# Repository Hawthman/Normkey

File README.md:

A custom 48 key split keyboard.

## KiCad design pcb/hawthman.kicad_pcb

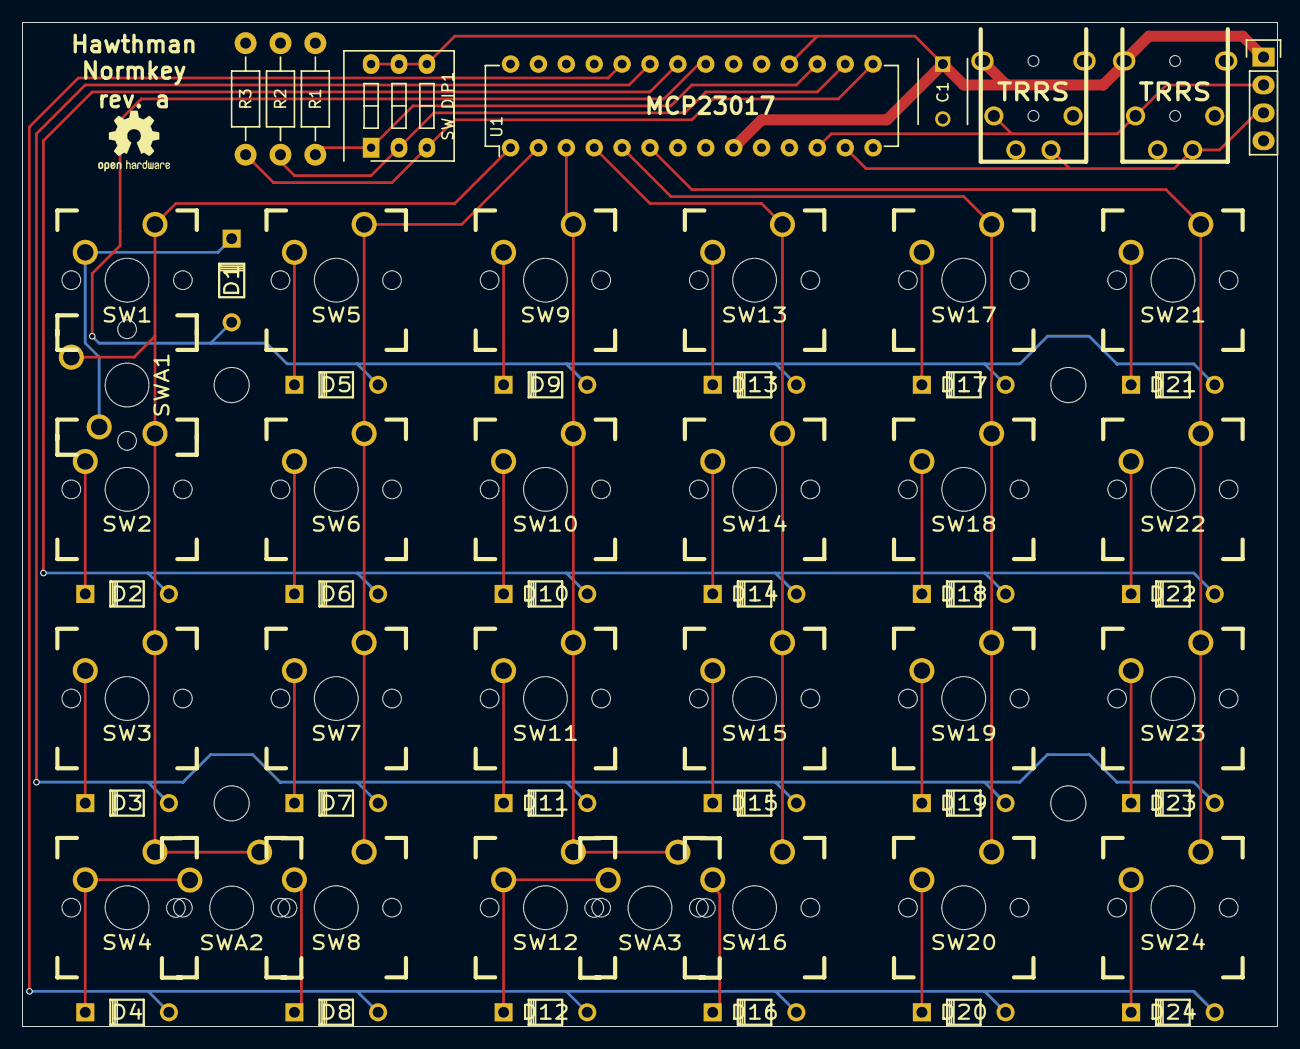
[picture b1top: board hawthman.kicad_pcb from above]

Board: 2 copper layers, 114.3 x 91.4 mm, 60 parts (0 on the bottom side), 41 nets.

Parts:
C1: 0.1uF; C_Disc_D6_P5
D1, D2, D3, D4, D5, D6, D7, D8, D9, D10, D11, D12, D13, D14, D15, D16, D17, D18, D19, D20, D21, D22, D23, D24: D; DIODE
J1, J2: TRRS; 4pin35mmAudio
J3: Test; Pin_Header_Straight_1x04
R1, R2, R3: 10k; Resistor_Horizontal_RM10mm
SW1, SW2, SW3, SW4, SW5, SW6, SW7, SW8, SW9, SW10, SW11, SW12, SW13, SW14, SW15, SW16, SW17, SW18, SW19, SW20, SW21, SW22, SW23, SW24: SW_PUSH; CHERRY_PCB_100H
SWA1, SWA2, SWA3: SW_PUSH; CHERRY_PLATE_200H
SW_DIP1: DIP3; SW_DIP_x3_Slide
U1: MCP23017; DIP-28_W7.62mm

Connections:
+5V: C1.1, J1.4, J2.4, J3.1, SW_DIP1.4, SW_DIP1.5, SW_DIP1.6, U1.9, U1.18
GND: C1.2, J1.1, J2.1, J3.4, R1.2, R2.2, R3.2, U1.10
unnamed: D1.2, SW1.2, SWA1.2
unnamed: D2.2, SW2.2
unnamed: D3.2, SW3.2
unnamed: D4.2, SW4.2, SWA2.2
unnamed: D5.2, SW5.2
unnamed: D6.2, SW6.2
unnamed: D7.2, SW7.2
unnamed: D8.2, SW8.2
unnamed: D9.2, SW9.2
unnamed: D10.2, SW10.2
unnamed: D11.2, SW11.2
unnamed: D12.2, SW12.2, SWA3.2
unnamed: D13.2, SW13.2
unnamed: D14.2, SW14.2
unnamed: D15.2, SW15.2
unnamed: D16.2, SW16.2
unnamed: D17.2, SW17.2
unnamed: D18.2, SW18.2
unnamed: D19.2, SW19.2
unnamed: D20.2, SW20.2
unnamed: D21.2, SW21.2
unnamed: D22.2, SW22.2
unnamed: D23.2, SW23.2
unnamed: D24.2, SW24.2
unnamed: R1.1, SW_DIP1.1, U1.17
unnamed: R2.1, SW_DIP1.2, U1.16
unnamed: R3.1, SW_DIP1.3, U1.15
col0: SW1.1, SW2.1, SW3.1, SW4.1, SWA1.1, SWA2.1, U1.1
col1: SW5.1, SW6.1, SW7.1, SW8.1, U1.2
col2: SW9.1, SW10.1, SW11.1, SW12.1, SWA3.1, U1.3
col3: SW13.1, SW14.1, SW15.1, SW16.1, U1.4
col4: SW17.1, SW18.1, SW19.1, SW20.1, U1.5
col5: SW21.1, SW22.1, SW23.1, SW24.1, U1.6
row0: D1.1, D5.1, D9.1, D13.1, D17.1, D21.1, U1.21
row1: D2.1, D6.1, D10.1, D14.1, D18.1, D22.1, U1.22
row2: D3.1, D7.1, D11.1, D15.1, D19.1, D23.1, U1.23
row3: D4.1, D8.1, D12.1, D16.1, D20.1, D24.1, U1.24
scl: J1.2, J2.2, J3.2, U1.12
sda: J1.3, J2.3, J3.3, U1.13

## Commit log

2016-12-05 Squashed 'firmware/tmk_core/' content from commit 3097c9e
    git-subtree-dir: firmware/tmk_core
    git-subtree-split: 3097c9ec7fc67756e93bce3c0041653707bff19f
2016-12-05 Add update_tmk.sh script
2016-12-05 Add basic keyboard firmware (stolen from hawthkey)
2016-12-05 Add Peter Fleury's i2cmaster library
2016-12-05 Add i2cmaster to build
2016-12-05 Update matrix to poll both sides from i2c
2016-12-05 Program using avrdude
2016-12-21 Add PCB files
    This is my first PCB. I have no idea if I got anything right, but I've
    printed it. We'll see in 4-8 weeks.
2016-12-21 Add README and a render
